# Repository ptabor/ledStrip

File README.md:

# ledStrip
Hobby project of (3-channel) addressable led-strips controller PCB and arduino code.

Features: 
  - power rating: 12V x 15A = 180 W combined (as designed, but depends on actual components you will use)
  - 3 channels (12V), each rated at 7A, having it's own fuse, 5V logic - tested on:
     - [WS2812B](https://www.amazon.com/stores/BTF-LIGHTING/page/0FF60378-45DE-44E7-B0D7-8F5CD6478971?ref_=ast_bln) strips.
     - [WS2815](https://www.amazon.com/stores/page/DC3DD961-F922-4197-AFD3-9C96122A1429?ingress=2&visitId=07e98571-6e49-4d4c-9a71-37c2eb7d5c01&ref_=ast_bln)
     - (but should work with any 12V power, 5V logic strips)
  - ESP32 (devkit C) powered, with Wifi support  - Web-Server control and remote firmware update 
  - [MSGEQ7](https://www.digikey.lu/htmldatasheets/production/2071107/0/0/1/MSGEQ7.pdf) spectrum analyzer connected to 3.5mm Audio Jack.
  - USB-A port (0.8A) to power the remote audio-player. 

## PCB

### Front

### Back

## Building with Arduino IDE:

Install in Arduine IDE board manager:
 -ESP32
 -ESP32 from expressif 

In Arduino IDE Library manager:
 - ESP32Encoder 0.10.2
  
## WARNING

THE SOFTWARE AND HARDWARE DESIGN IS PROVIDED “AS IS”, WITHOUT WARRANTY OF ANY KIND, EXPRESS OR IMPLIED, 
INCLUDING BUT NOT LIMITED TO THE WARRANTIES OF MERCHANTABILITY, 
FITNESS FOR A PARTICULAR PURPOSE AND NONINFRINGEMENT. 
IN NO EVENT SHALL THE AUTHORS OR COPYRIGHT HOLDERS BE LIABLE FOR ANY CLAIM, 
DAMAGES OR OTHER LIABILITY, WHETHER IN AN ACTION OF CONTRACT, TORT OR OTHERWISE, 
ARISING FROM, OUT OF OR IN CONNECTION WITH THE SOFTWARE OR THE USE OR OTHER DEALINGS IN THE SOFTWARE.

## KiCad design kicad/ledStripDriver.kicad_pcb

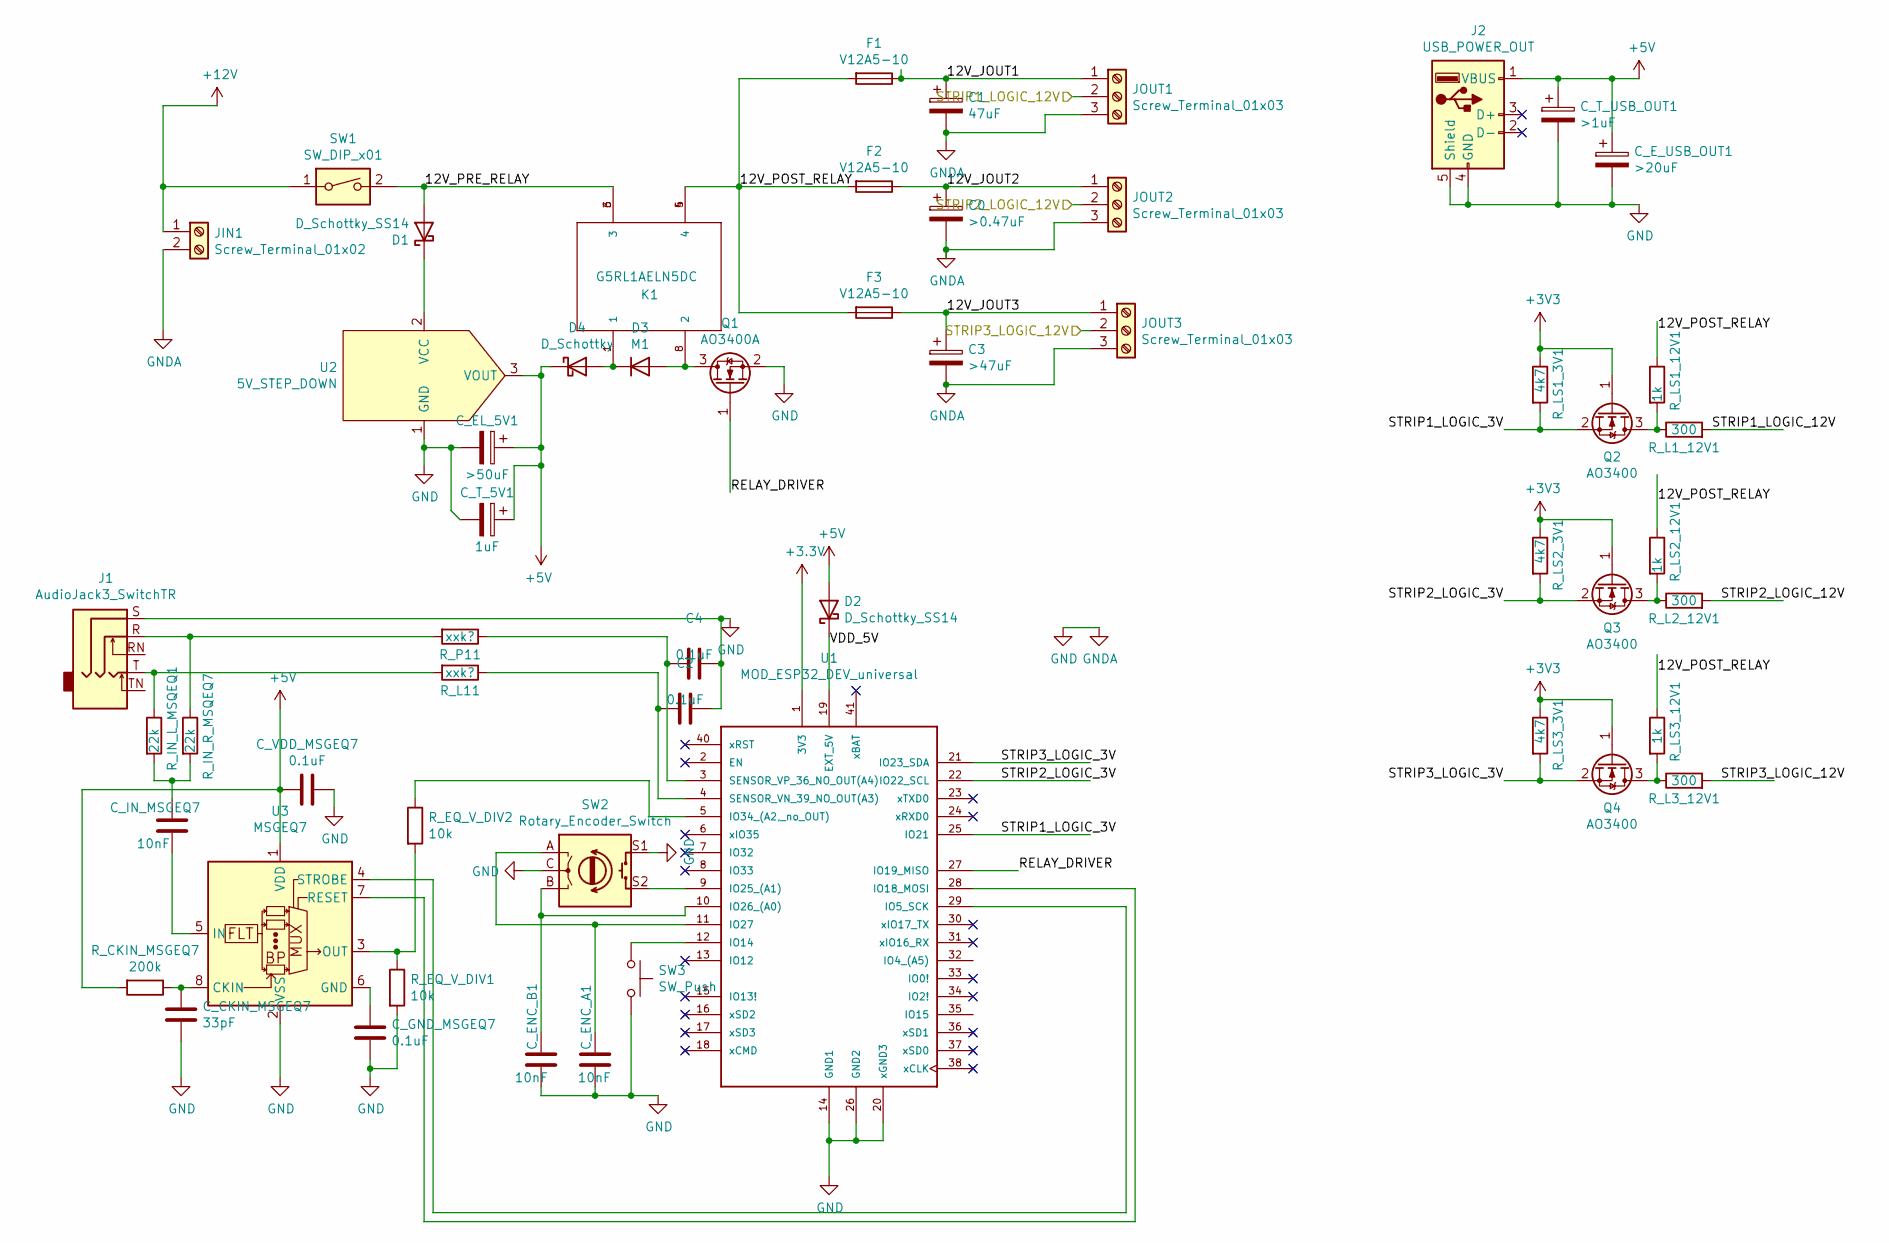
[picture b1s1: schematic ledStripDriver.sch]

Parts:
C0: >0.47uF; CP_Radial_D8.0mm_P3.80mm
C1: 47uF; CP_Radial_D8.0mm_P3.80mm
C2, C4: 0.1uF; C_0805_2012Metric_Pad1.15x1.40mm_HandSolder
C3: >47uF; CP_Radial_D8.0mm_P3.80mm
C_CKIN_MSGEQ7: 33pF; C_0805_2012Metric_Pad1.15x1.40mm_HandSolder
C_EL_5V1: >50uF; CP_Elec_6.3x5.4
C_ENC_A1: 10nF; C_0805_2012Metric_Pad1.15x1.40mm_HandSolder
C_ENC_B1: 10nF; C_0805_2012Metric_Pad1.15x1.40mm_HandSolder
C_E_USB_OUT1: >20uF; CP_Elec_6.3x5.4
C_GND_MSGEQ7: 0.1uF; C_0805_2012Metric_Pad1.15x1.40mm_HandSolder
C_IN_MSGEQ7: 10nF; C_0805_2012Metric_Pad1.15x1.40mm_HandSolder
C_T_5V1: 1uF; C_0805_2012Metric_Pad1.15x1.40mm_HandSolder
C_T_USB_OUT1: >1uF; C_0805_2012Metric_Pad1.15x1.40mm_HandSolder
C_VDD_MSGEQ7: 0.1uF; C_0805_2012Metric_Pad1.15x1.40mm_HandSolder
D1, D2: D_Schottky_SS14; D_SMA_Handsoldering
D3: M1; D_SMA_Handsoldering
D4: D_Schottky; D_SMA_Handsoldering
F1, F2, F3: V12A5-10; Fuseholder_Cylinder-5x20mm_Stelvio-Kontek_PTF78_Horizontal_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
J1: AudioJack3_SwitchTR; AudioJack3_SwitchTR_PJ3024
J2: USB_POWER_OUT; USB_A_CONNFLY_DS1095-WNR0
JIN1: Screw_Terminal_01x02; TerminalBlock_RND_205-00023_1x02_P10.00mm_Horizontal(2mmdri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
JOUT1, JOUT2, JOUT3: Screw_Terminal_01x03; TerminalBlock_RND_205-00002_1x03_P5.00mm_Horizontal
K1: G5RL1AELN5DC; RELAY_G5RL1AELN12DC
Q1: AO3400A; SOT-23
Q2, Q3, Q4: AO3400; SOT-23
R_CKIN_MSGEQ7: 200k; R_0805_2012Metric_Pad1.15x1.40mm_HandSolder
R_EQ_V_DIV1, R_EQ_V_DIV2: 10k; R_0805_2012Metric_Pad1.15x1.40mm_HandSolder
R_IN_L_MSQEQ1: 22k; R_0805_2012Metric_Pad1.15x1.40mm_HandSolder
R_IN_R_MSQEQ7: 22k; R_0805_2012Metric_Pad1.15x1.40mm_HandSolder
R_L1_12V1, R_L2_12V1, R_L3_12V1: 300; R_0805_2012Metric_Pad1.15x1.40mm_HandSolder
R_L11: xxk?; R_0805_2012Metric_Pad1.15x1.40mm_HandSolder
R_LS1_3V1, R_LS2_3V1, R_LS3_3V1: 4k7; R_0805_2012Metric_Pad1.15x1.40mm_HandSolder
R_LS1_12V1, R_LS2_12V1, R_LS3_12V1: 1k; R_0805_2012Metric_Pad1.15x1.40mm_HandSolder
R_P11: xxk?; R_0805_2012Metric_Pad1.15x1.40mm_HandSolder
SW1: SW_DIP_x01; ROCKER_SWITCH_7x0.5mm
SW2: Rotary_Encoder_Switch; RotaryEncoder_Alps_EC12E-Switch_Vertical_H20mm
SW3: SW_Push; SW_PUSH_6mm
U1: MOD_ESP32_DEV_universal; MOD_ESP32_DEV_DEVKITC-32D
U2: 5V_STEP_DOWN; DC_STEP_DOWN_MODULE_223_17
U3: MSGEQ7; DIP-8_W7.62mm_Socket

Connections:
+5V: C_EL_5V1.1, C_E_USB_OUT1.1, C_T_5V1.1, C_T_USB_OUT1.1, C_VDD_MSGEQ7.2, D2.2 (A), D4.1 (K), J2.1 (VBUS), R_CKIN_MSGEQ7.2, U2.3 (VOUT), U3.1 (VDD)
+12V: JIN1.1, SW1.1
/12V_JOUT1: C1.1, F1.1, JOUT1.1
/12V_JOUT2: C0.1, F2.1, JOUT2.1
/12V_JOUT3: C3.1, F3.1, JOUT3.1
/12V_POST_RELAY: F1.2, F2.2, F3.2, K1.4, K1.5 (4), R_LS1_12V1.1, R_LS2_12V1.1, R_LS3_12V1.1
/12V_PRE_RELAY: D1.2 (A), K1.3, K1.6 (3), SW1.2
/RELAY_DRIVER: Q1.1 (G), U1.27 (IO19_MISO)
/STRIP1_LOGIC_3V: Q2.2 (S), R_LS1_3V1.2, U1.25 (IO21)
/STRIP1_LOGIC_12V: JOUT1.2, R_L1_12V1.2
/STRIP2_LOGIC_3V: Q3.2 (S), R_LS2_3V1.2, U1.22 (IO22_SCL)
/STRIP2_LOGIC_12V: JOUT2.2, R_L2_12V1.2
/STRIP3_LOGIC_3V: Q4.2 (S), R_LS3_3V1.2, U1.21 (IO23_SDA)
/STRIP3_LOGIC_12V: JOUT3.2, R_L3_12V1.2
/VDD_5V: D2.1 (K), U1.19 (EXT_5V)
GND: C0.2, C1.2, C2.1, C3.2, C4.1, C_CKIN_MSGEQ7.2, C_EL_5V1.2, C_ENC_A1.2, C_ENC_B1.2, C_E_USB_OUT1.2, C_GND_MSGEQ7.2, C_T_5V1.2, C_T_USB_OUT1.2, C_VDD_MSGEQ7.1, J1.S, J2.4 (GND), J2.5 (Shield), JIN1.2, JOUT1.3, JOUT2.3, JOUT3.3, Q1.2 (S), R_EQ_V_DIV1.2, SW2.C, SW2.S1, SW3.2, U1.14 (GND1), U1.20 (xGND3), U1.26 (GND2), U2.1 (GND), U3.2 (VSS)
unnamed: C2.2, R_L11.1, U1.4 (SENSOR_VN_39_NO_OUT(A3))
unnamed: C4.2, R_P11.1, U1.3 (SENSOR_VP_36_NO_OUT(A4))
unnamed: C_CKIN_MSGEQ7.1, R_CKIN_MSGEQ7.1, U3.8 (CKIN)
unnamed: C_ENC_A1.1, SW2.A, U1.11 (IO27)
unnamed: C_ENC_B1.1, SW2.B, U1.10 (IO26_(A0))
unnamed: C_GND_MSGEQ7.1, U3.6 (GND)
unnamed: C_IN_MSGEQ7.1, R_IN_L_MSQEQ1.2, R_IN_R_MSQEQ7.2
unnamed: C_IN_MSGEQ7.2, U3.5 (IN)
unnamed: D1.1 (K), U2.2 (VCC)
unnamed: D3.1 (K), D4.2 (A), K1.1
unnamed: D3.2 (A), K1.8 (2), Q1.3 (D)
unnamed: J1.R, R_IN_R_MSQEQ7.1, R_P11.2
unnamed: J1.T, R_IN_L_MSQEQ1.1, R_L11.2
unnamed: Q2.3 (D), R_L1_12V1.1, R_LS1_12V1.2
unnamed: Q3.3 (D), R_L2_12V1.1, R_LS2_12V1.2
unnamed: Q4.3 (D), R_L3_12V1.1, R_LS3_12V1.2
unnamed: R_EQ_V_DIV1.1, R_EQ_V_DIV2.2, U3.3 (OUT)
unnamed: R_EQ_V_DIV2.1, U1.5 (IO34_(A2,_no_OUT))
unnamed: SW2.S2, U1.9 (IO25_(A1))
unnamed: SW3.1, U1.12 (IO14)
unnamed: U1.28 (IO18_MOSI), U3.7 (RESET)
unnamed: U1.29 (IO5_SCK), U3.4 (STROBE)

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
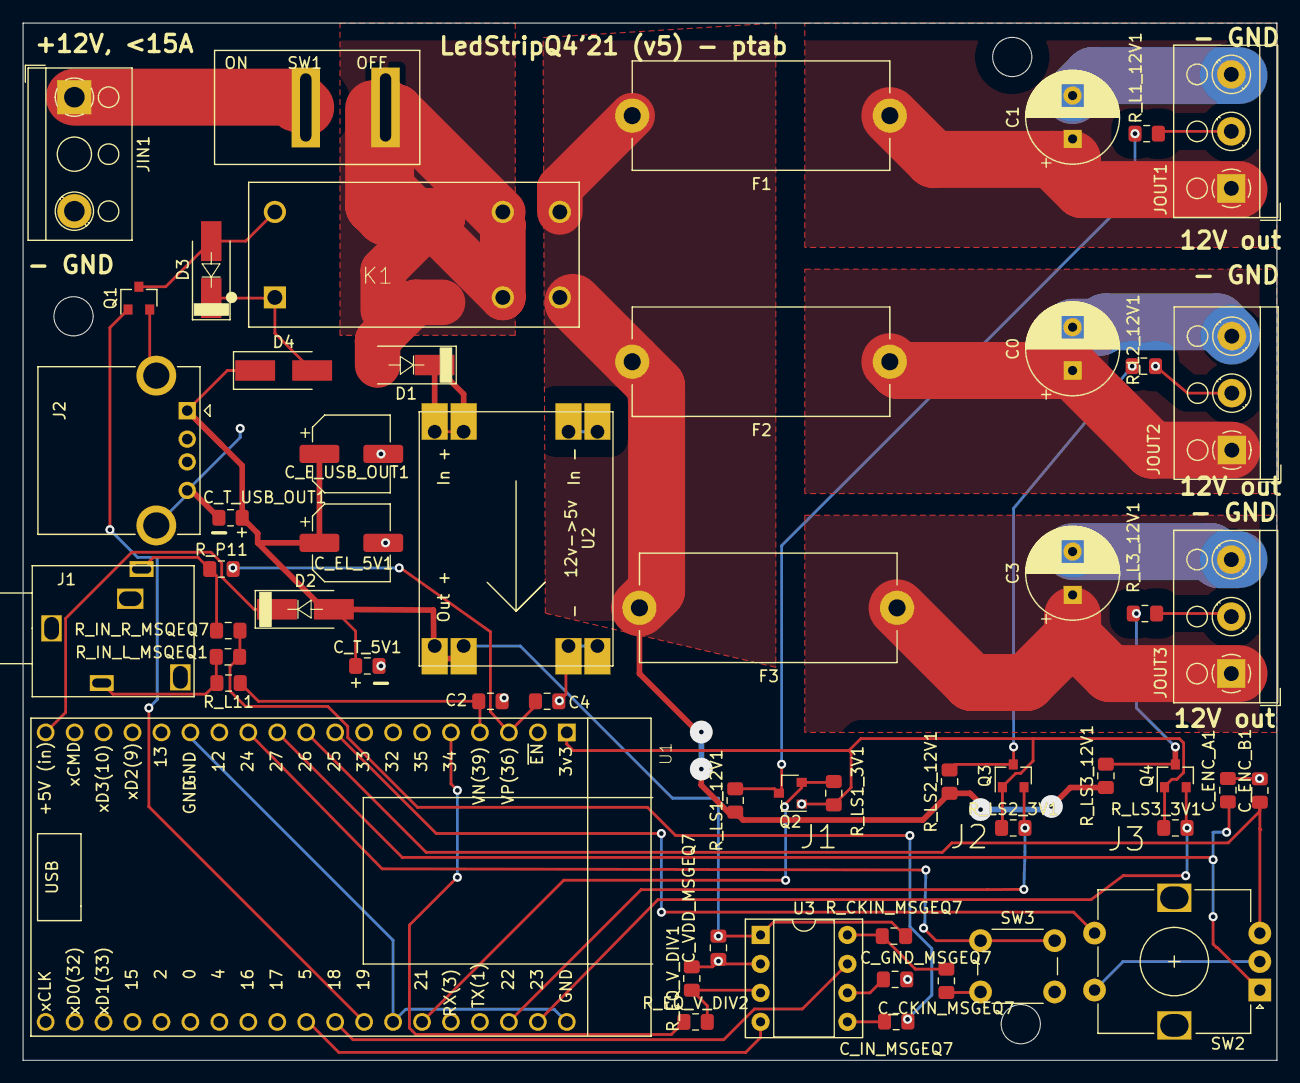
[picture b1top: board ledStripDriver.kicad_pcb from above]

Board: 2 copper layers, 110.0 x 91.0 mm, 55 parts (0 on the bottom side), 39 nets.

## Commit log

2020-02-21 Before PCB Manufacturing Q1'2020
2020-02-21 GitIgnore
2020-03-03 Confirmed to work version of arduino software (1-strip on WS2815 showing rainbow). Running on PCB Q1-2020.
2020-03-22 Fixed.
2020-03-22 KiCad fixes: flip Jack, add resistor on 12V logic to protect LEDs.
2020-08-23 Modified schema to consiste MSQ spectrum analyzer. No PCB updates yet.
2020-08-23 Refreshed PCB and footprints of (Fuse holder, Rocker switch, Screw-terminal for input)
2020-08-26 PCB v2 - with hardware spectrum analyzer.
2020-10-04 Revision 2 - Q3'2020 -> Printed board (rev2), Software confirmed to work. No support for Jack yet.
2020-10-05 Blink to Music on MSGEQ07 - prototype
2020-10-10 PCB v3: Hopefully manufacturing ready.
2020-10-16 With charging port.
2020-12-06 v3 - working and split between files. StroboRainbows.
2020-12-06 Encoder programmed.
2021-03-13 v4 - preprod
2021-11-27 Checkpoint before 2021 christmast.
2021-12-12 V4-board. Christmat 2021 - before implementing Wifi support.
2022-01-16 Rainbow is pulsing. MDNS correctly configured. drawMap(...) is not injecting any delay.
2023-02-01 Added: Google colors, ukraine, /brightness?c=10 web settings.
2023-02-08 Adding Google->Snowflake transition.
2023-02-09 Improve google colors.
2023-02-11 Move passwords to a separate file.
2023-02-11 Files reorganization.
2023-02-11 Link components to 3d images. Render back and front.
2023-02-11 Adding AVT project (https://sklep.avt.pl/avt5712.html) that demonastrates application on MSGEQ7.
2023-02-11 Protect password from being accidentally published.
2025-01-15 Updated to Arduino/ESP32 3.0 version (mostly RMT interface).
2025-01-15 Fix.
2025-01-19 Google Home Support. Http server rewritten to ESP
2025-02-03 First version of home assistant support in ledStrip.
2025-02-03 Added readme.
2025-02-03 Done.
